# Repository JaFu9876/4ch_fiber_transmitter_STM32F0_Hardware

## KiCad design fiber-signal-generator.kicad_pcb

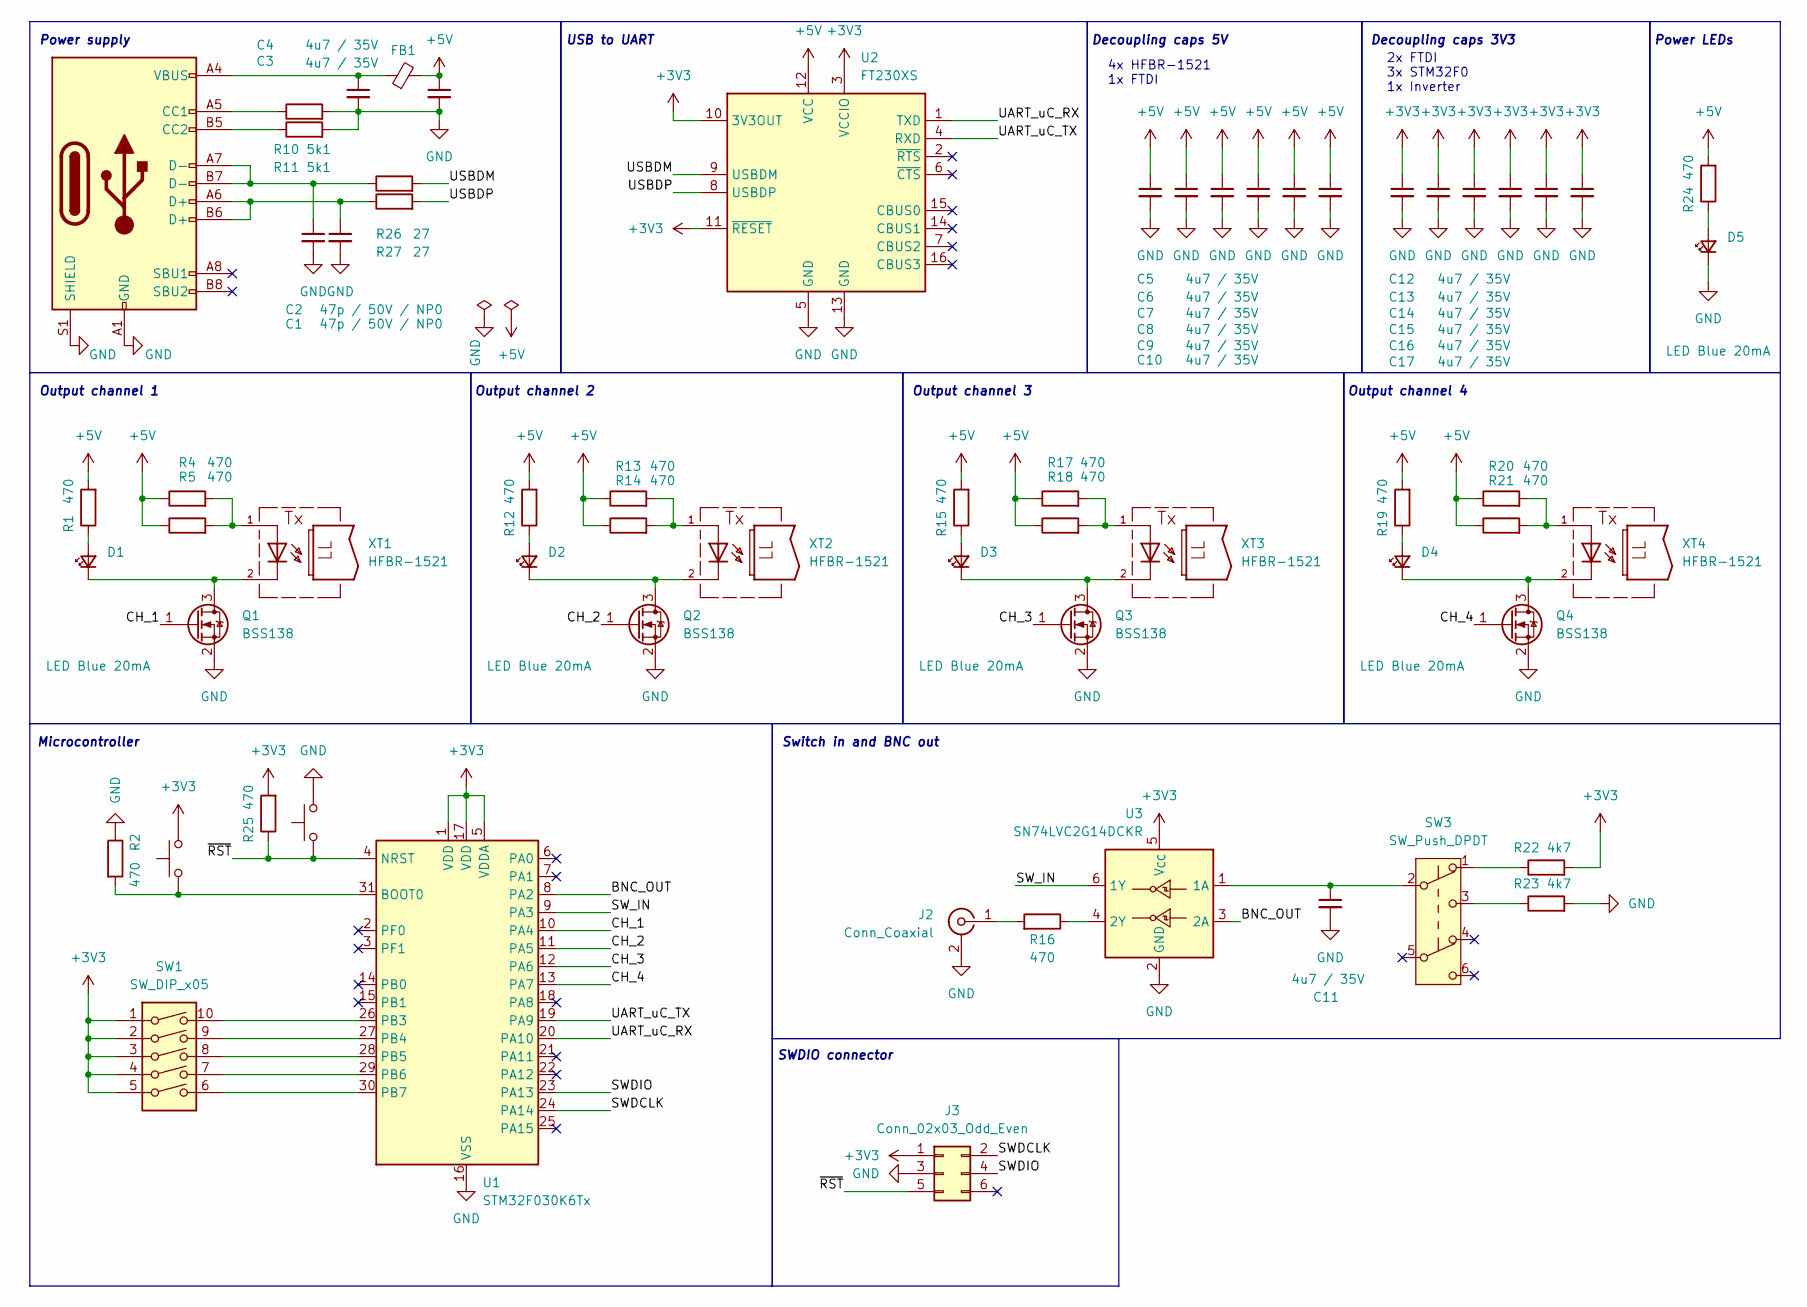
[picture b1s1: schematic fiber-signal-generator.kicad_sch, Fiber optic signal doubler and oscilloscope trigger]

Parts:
C1, C2: 47p / 50V / NP0; C_0603_1608Metric; LCSC C105622
C3, C4, C5, C6, C7, C8, C9, C10, C11, C12, C13, C14, C15, C16, C17: 4u7 / 35V; C_0603_1608Metric; LCSC C307467
D1, D2, D3, D4, D5: LED Blue 20mA; LED_0603_1608Metric; LCSC C965807
FB1: FerriteBead_Small; L_0805_2012Metric; LCSC C78138
J1: USB_C_Receptacle_USB2.0_16P; USB_C_Receptacle_G-Switch_GT-USB-7010ASV; LCSC C393939
J2: Conn_Coaxial; BNC_Amphenol_B6252HB-NPP3G-50_Horizontal; LCSC C2837587
J3: Conn_02x03_Odd_Even; PinHeader_2x03_P2.54mm_Vertical; LCSC C7501274
Q1, Q2, Q3, Q4: BSS138; SOT-23; LCSC C7420339
R1, R2, R4, R5, R12, R13, R14, R15, R16, R17, R18, R19, R20, R21, R24, R25: 470; R_0603_1608Metric; LCSC C384220
R10, R11: 5k1; R_0603_1608Metric; LCSC C23186
R22, R23: 4k7; R_0603_1608Metric; LCSC C23162
R26, R27: 27; R_0603_1608Metric; LCSC C25190
SW1: SW_DIP_x05; SW_DIP_SPSTx05_Slide_6.7x14.26mm_W8.61mm_P2.54mm_LowProfile; LCSC C319036
SW2, SW4: SW_Push; SW_Push_1P1T_NO_CK_KMR2; LCSC C221680
SW3: SW_Push_DPDT; SW_Push_2P2T_Toggle_CK_PVA2OAH5xxxxxxV2; LCSC C2848957
U1: STM32F030K6Tx; LQFP-32_7x7mm_P0.8mm; LCSC C46830
U2: FT230XS; SSOP-16_3.9x4.9mm_P0.635mm; LCSC C69082
U3: SN74LVC2G14DCKR; SOT-363_SC-70-6; LCSC C37361
XT1, XT3: HFBR-1521; HFBR-252x; LCSC C188712
XT2, XT4: HFBR-1521; HFBR-252x; MPN HFBR-1521; LCSC C188712

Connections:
+3V3: C12.1, C13.1, C14.1, C15.1, C16.1, C17.1, J3.1, R22.2, R25.2, SW1.1, SW1.2, SW1.3, SW1.4, SW1.5, SW2.2, U1.1 (VDD), U1.5 (VDDA), U1.17 (VDD), U2.3 (VCCIO), U2.10 (3V3OUT), U2.11 (~RESET), U3.5 (V_{CC})
+5V: C4.1, C5.1, C6.1, C7.1, C8.1, C9.1, C10.1, FB1.2, R1.2, R4.1, R5.1, R12.2, R13.1, R14.1, R15.2, R17.1, R18.1, R19.2, R20.1, R21.1, R24.2, U2.12 (VCC)
/BNC_OUT: U1.8 (PA2), U3.3 (2A)
/CH_1: Q1.1 (G), U1.10 (PA4)
/CH_2: Q2.1 (G), U1.11 (PA5)
/CH_3: Q3.1 (G), U1.12 (PA6)
/CH_4: Q4.1 (G), U1.13 (PA7)
/SWDCLK: J3.2, U1.24 (PA14)
/SWDIO: J3.4, U1.23 (PA13)
/SW_IN: U1.9 (PA3), U3.6 (1Y)
/UART_uC_RX: U1.20 (PA10), U2.1 (TXD)
/UART_uC_TX: U1.19 (PA9), U2.4 (RXD)
/USBDM: R26.2, U2.9 (USBDM)
/USBDP: R27.2, U2.8 (USBDP)
/~RST: J3.5, R25.1, SW4.1, U1.4 (NRST)
GND: C1.2, C2.2, C3.2, C4.2, C5.2, C6.2, C7.2, C8.2, C9.2, C10.2, C11.2, C12.2, C13.2, C14.2, C15.2, C16.2, C17.2, D5.1 (K), J1.A1 (GND), J1.A12 (GND), J1.B1 (GND), J1.B12 (GND), J1.S1 (SHIELD), J2.2 (Ext), J3.3, Q1.2 (S), Q2.2 (S), Q3.2 (S), Q4.2 (S), R2.1, R10.2, R11.2, R23.2, SW4.2, U1.16 (VSS), U1.32 (VSS), U2.5 (GND), U2.13 (GND), U3.2 (GND)
unnamed: C1.1, J1.A7 (D-), J1.B7 (D-), R26.1
unnamed: C2.1, J1.A6 (D+), J1.B6 (D+), R27.1
unnamed: C3.1, FB1.1, J1.A4 (VBUS), J1.A9 (VBUS), J1.B4 (VBUS), J1.B9 (VBUS)
unnamed: D1.2 (A), R1.1
unnamed: D1.1 (K), Q1.3 (D), XT1.2
unnamed: D2.2 (A), R12.1
unnamed: D2.1 (K), Q2.3 (D), XT2.2
unnamed: D3.2 (A), R15.1
unnamed: D3.1 (K), Q3.3 (D), XT3.2
unnamed: D4.2 (A), R19.1
unnamed: D4.1 (K), Q4.3 (D), XT4.2
unnamed: D5.2 (A), R24.1
unnamed: J1.A5 (CC1), R10.1
unnamed: J1.B5 (CC2), R11.1
unnamed: J2.1 (In), R16.2
unnamed: R4.2, R5.2, XT1.1
unnamed: R13.2, R14.2, XT2.1
unnamed: R17.2, R18.2, XT3.1
unnamed: R20.2, R21.2, XT4.1
unnamed: R22.1, SW3.1 (A)
unnamed: R23.1, SW3.3 (C)
unnamed: R2.2, SW2.1, U1.31 (BOOT0)
unnamed: SW1.10, U1.26 (PB3)
unnamed: SW1.9, U1.27 (PB4)
unnamed: SW1.8, U1.28 (PB5)
unnamed: SW1.7, U1.29 (PB6)
unnamed: SW1.6, U1.30 (PB7)
unnamed: C11.1, SW3.2 (B), U3.1 (1A)
unnamed: R16.1, U3.4 (2Y)

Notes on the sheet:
Power supply
4x HFBR-1521 1x FTDI
Output channel 4
Output channel 1
Switch in and BNC out
Output channel 3
Decoupling caps 3V3
SWDIO connector
Output channel 2
USB to UART
Microcontroller
Power LEDs
2x FTDI 3x STM32F0 1x Inverter
Decoupling caps 5V

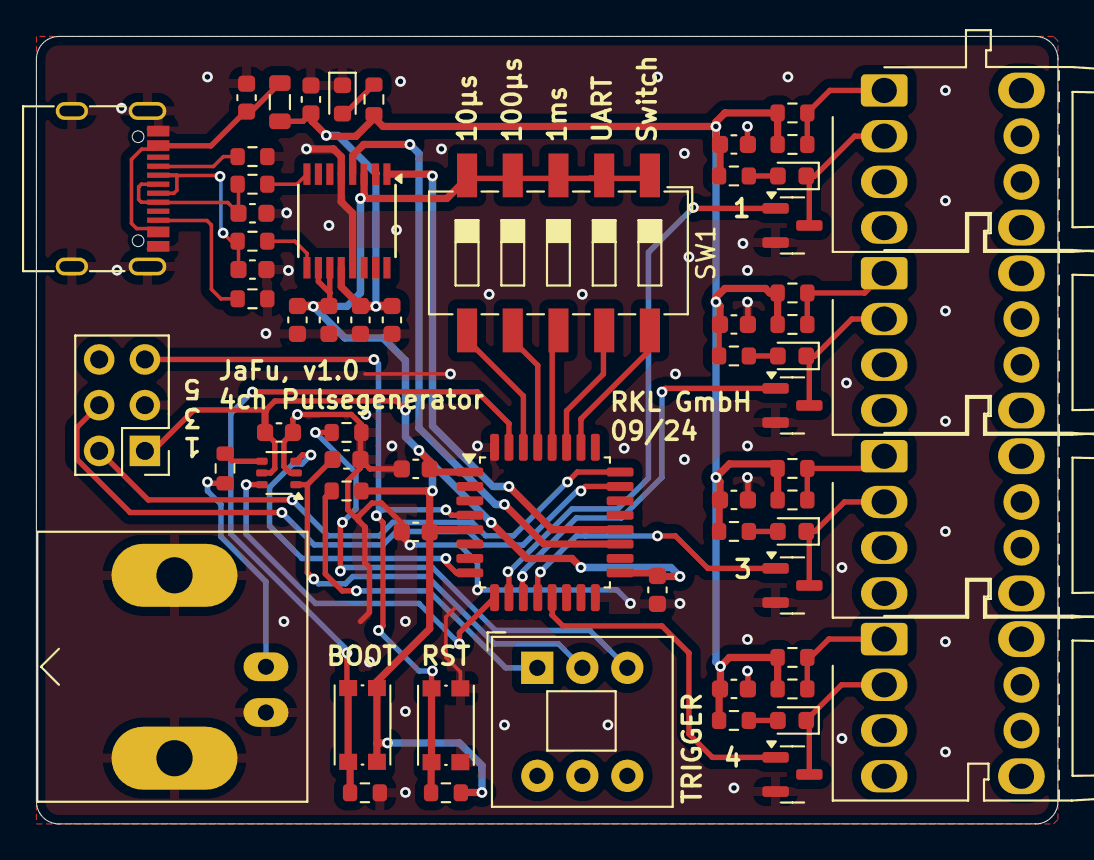
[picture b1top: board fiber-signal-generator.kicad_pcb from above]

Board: 2 copper layers, 56.8 x 43.8 mm, 63 parts (0 on the bottom side), 45 nets.

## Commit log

2025-01-20 Initial upload project file
